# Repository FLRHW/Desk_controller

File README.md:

# Desk Controller

**A custom KiCad PCB design for a motorised sit–stand desk controller with a touchscreen human–machine interface (HMI).**

[Hardware design](https://github.com/FLRHW/Desk_controller) · [Online documentation](https://flrhw.github.io/Desk_controller/) · [Firmware repository](https://github.com/FLRHW/Desk_controller_source) · [3D renders](output/3d/) · [Manufacturing outputs](output/)

This repository contains the KiCad hardware design for a desk controller that brings together the user interface, control electronics, motor interface and end-of-travel sensing on one board. It is intended to interface with an external desk mechanism, motor/gearbox/encoder assembly and power supply. The project started as a personal engineering build; the design is published so others can inspect, learn from, or adapt it at their own risk.

Beyond the intended application, the repository documents the design workflow—from system-level architecture and hierarchical schematics through PCB layout, design checks and automated fabrication/assembly deliverables.

> **Project scope:** This repository documents the controller **hardware**. The desk mechanism, motor assembly and external power supply are shown for context and are not part of the PCB design. Do not assume the design is production-ready or safe to connect to a desk without independent electrical, mechanical and functional validation.

## System overview

The design is organised into these functional blocks:

| Block | Purpose |
| --- | --- |
| Microcontroller / control logic | Coordinates the user interface and motor-control signals. |
| Touch display | Local human–machine interface for operating the desk. |
| Servomotor interface | Motor power-drive interface and encoder signal conditioning. |
| Limit-switch interface | Connections and conditioning for end-of-travel signals. |
| 3.3 V DC/DC conversion | Low-voltage supply for the control electronics. |
| Power-supply interface | Connection to the external power source. |

See [`System_overview.kicad_sch`](System_overview.kicad_sch) and [`Block_diagram.kicad_sch`](Block_diagram.kicad_sch) for the system-level drawings. The hierarchical schematic files provide the electrical details.

## PCB renders and design outputs

The renders below are generated from the KiCad PCB design as part of the automated documentation workflow.

| Top view | Bottom view |
| --- | --- |
|  |  |

Additional renders and design files:

- [All 3D renders and models](output/3d/) — angled, top and bottom PNG views, plus the [STEP model](output/3d/Desk_controller-3D.step).
- [Fabrication documentation and files](output/fabrication/) — fabrication drawings, Gerbers and drill outputs (where generated).
- [Assembly documentation and files](output/assembly/) — assembly drawings, BOM/iBOM and placement data (where generated).
- [Design checks and build reports](output/reports/) — ERC/DRC and generation logs.
- [Browse generated outputs online](https://flrhw.github.io/Desk_controller/) — published HTML index with links to PDFs, renders, interactive BOM and downloadable manufacturing files.
- [Generated files in the repository](output/) — full output tree; the [local HTML index](output/index.html) can also be opened after cloning.
- [Native PCB layout](Desk_controller.kicad_pcb) and [hierarchical schematic](Desk_controller.kicad_sch) — editable KiCad design sources.

The generated files are published to make the design easier to review and reproduce. **Their presence does not imply that the PCB, assembly or motor-control system has been manufactured, tested or validated.** Check the current outputs and reports before considering fabrication.

## Firmware

The firmware is developed separately in **[FLRHW/Desk_controller_source](https://github.com/FLRHW/Desk_controller_source)**. It is **under development and not yet usable**. Please consult that repository for its latest implementation and status; firmware progress is intentionally not duplicated here to avoid maintaining two status reports.

## Repository contents

| Path | Description |
| --- | --- |
| [`Desk_controller.kicad_pro`](Desk_controller.kicad_pro) | KiCad project settings. |
| [`Desk_controller.kicad_sch`](Desk_controller.kicad_sch) | Root hierarchical schematic. |
| [`Desk_controller.kicad_pcb`](Desk_controller.kicad_pcb) | PCB layout. |
| `Microcontroller.kicad_sch` | Control electronics. |
| `Display.kicad_sch` | Display interface. |
| `Servomotor_interface.kicad_sch` | Motor driver and encoder interface circuitry. |
| `Limit_switch_interface.kicad_sch` | Limit-switch interface circuitry. |
| `DCDC_converter_3V3.kicad_sch` | 3.3 V supply stage. |
| `Interface_*.kicad_sch` | External connection/interface drawings. |
| `output/` | Generated documentation and manufacturing exports. |
| `config.kibot.yaml` | KiBot output and documentation configuration. |
| `.github/workflows/`, `ci/`, `scripts/`, `templates/` | Automated generation, helper scripts and drawing worksheets inherited from the KiCad starter. |

## Opening the design

1. Install [KiCad 10](https://www.kicad.org/).
2. Clone the repository:

   ```bash
   git clone https://github.com/FLRHW/Desk_controller.git
   cd Desk_controller
   ```

3. Open `Desk_controller.kicad_pro` in KiCad.
4. Open the schematic editor to navigate the hierarchical sheets, or the PCB editor to inspect the board layout.
5. Run KiCad's Electrical Rules Checker (ERC) and Design Rules Checker (DRC) after making changes, and review the reports before fabricating a board.

This is an **existing project**, not a fresh copy of the starter template: you do not need to run the template's project-creation instructions to open it.

## Generated documentation and manufacturing files

The repository uses [KiBot](https://github.com/INTI-CMNB/KiBot) and GitHub Actions to generate design documentation and manufacturing outputs. Depending on the active `config.kibot.yaml` settings and the latest completed workflow, `output/` can include:

- Schematic, assembly and fabrication PDFs
- ERC/DRC reports
- Bill of materials (BOM) and interactive HTML BOM
- Gerber files and Excellon drill files
- Pick-and-place files and 3D STEP exports
- Optional renders and manufacturing ZIP packages

Browse the [online documentation](https://flrhw.github.io/Desk_controller/), or open `output/index.html` locally after cloning. The website is updated by successful default-branch builds when GitHub Pages publishing is enabled and shows the latest deployed outputs; use a release tag for a fixed snapshot. The original template's documentation contains more details on the export system: [FLRHW KiCad Starter](https://github.com/FLRHW/KiCad_starter).

**Before ordering PCBs:** inspect the actual Gerbers, drill data, stack-up, BOM and fabrication notes. Generated outputs and a passing automation run are not substitutes for electrical and safety verification; inspect ERC/DRC reports separately.

## Development status

This repository contains an evolving hardware design. The presence of schematics, PCB files or manufacturing exports does **not** imply that a physical prototype has been built, tested or validated. Anyone building or operating hardware based on this design must independently assess the risks, verify that the complete system is safe for its intended use, and implement and validate appropriate safeguards before putting it into service. The availability of design files or manufacturing outputs is not evidence of safety or fitness for use. For firmware progress and readiness, refer to the [firmware repository](https://github.com/FLRHW/Desk_controller_source).

## Safety

Motorised desk systems can cause injury or property damage. Before operating hardware based on this design, independently verify power-stage ratings, polarity and protection; limit-switch behaviour; motor direction and feedback; fault handling; and the ability to stop motion reliably. Never rely on software alone as the sole protection against unintended travel.

In the author's personal installation, a manually operated power-disconnect switch is fitted upstream of the power supply feeding the controller. This arrangement is described for reference only and has not been established as a sufficient safety measure for other installations.

Anyone reproducing or adapting this design is responsible for independently assessing the hazards of their complete system, implementing appropriate protective measures, and verifying their effectiveness before use. No particular safety arrangement is prescribed or guaranteed by this project.

## Licensing and reuse

This repository contains material covered by **two separate licences**, according to the origin and purpose of the files:

- **Original hardware design — [CERN-OHL-P-2.0](LICENSE):** The Desk Controller schematics, PCB layout and associated original design and manufacturing files are released under the CERN Open Hardware Licence Version 2 — Permissive. The [`LICENSE`](LICENSE) file contains the hardware licence text.
- **Inherited KiCad starter infrastructure — [MIT](LICENSE-MIT):** Applicable files retained or adapted from [FLRHW/KiCad_starter](https://github.com/FLRHW/KiCad_starter), such as automation scripts, CI workflows and templates, remain under the MIT licence, with their original copyright notices preserved. The [`LICENSE-MIT`](LICENSE-MIT) file contains the corresponding MIT licence and notices.

These licences apply to their respective materials; the presence of both files does **not** mean that the entire repository is offered under a choice of either licence. Third-party dependencies or assets may have their own terms. The [firmware](https://github.com/FLRHW/Desk_controller_source) is maintained separately and is subject to the licensing terms in that repository.

**Disclaimer:** This is a personal engineering project shared **as is**, without warranty of safety, fitness for a particular purpose, completeness or correct operation. Anyone reusing, building, modifying or operating the design is responsible for their own engineering review, applicable regulatory requirements, testing and safeguards. The applicable licence texts govern warranty disclaimers and limitations of liability; this summary does not replace their terms.

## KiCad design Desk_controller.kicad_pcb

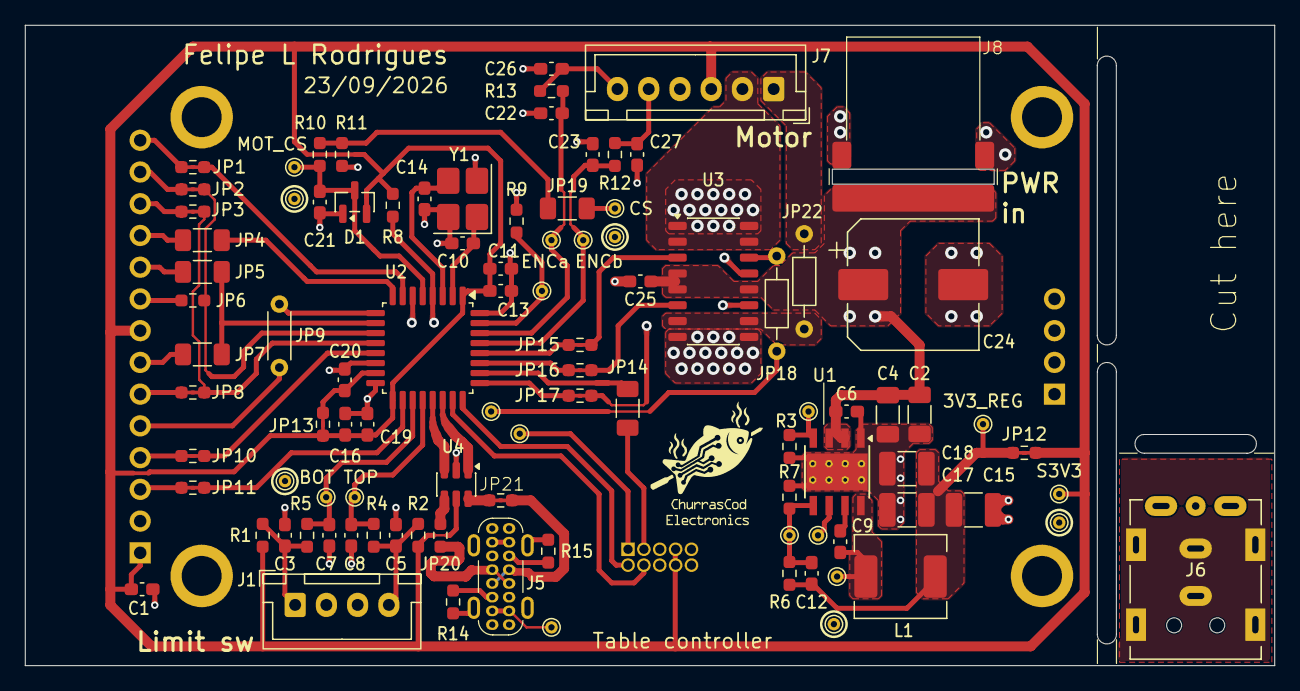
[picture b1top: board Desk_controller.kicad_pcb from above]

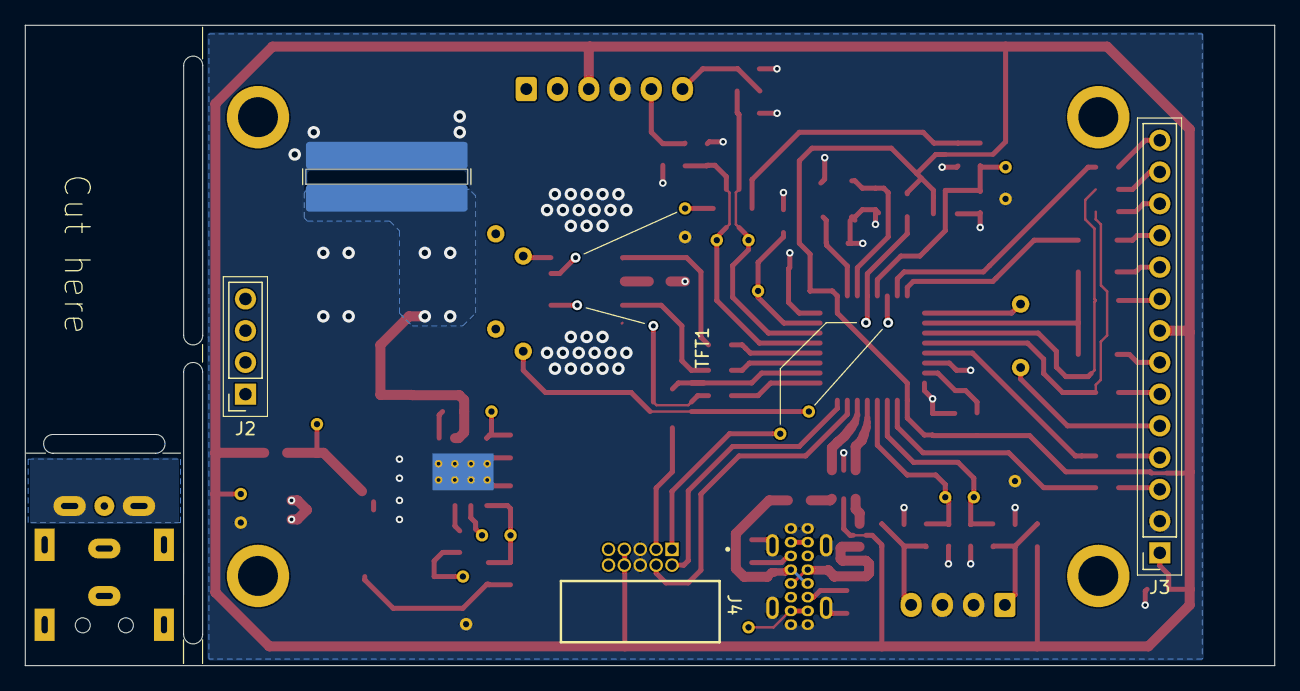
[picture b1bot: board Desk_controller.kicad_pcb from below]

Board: 2 copper layers, 100.0 x 51.2 mm, 105 parts (7 on the bottom side), 74 nets.

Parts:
C1, C6, C9, C13, C19, C20, C25: 100n; C_0603_1608Metric_Pad1.08x0.95mm_HandSolder
C2, C4: 4.7u; C_1206_3216Metric_Pad1.33x1.80mm_HandSolder
C3, C5, C26, C27: 10n; C_0603_1608Metric_Pad1.08x0.95mm_HandSolder
C7, C8, C21, C22, C23: 1n; C_0603_1608Metric_Pad1.08x0.95mm_HandSolder
C10, C14: 22p; C_0603_1608Metric_Pad1.08x0.95mm_HandSolder
C11, C16: 1u; C_0603_1608Metric_Pad1.08x0.95mm_HandSolder
C12: 33p; C_0603_1608Metric_Pad1.08x0.95mm_HandSolder
C15, C17, C18: 22u; C_1210_3225Metric_Pad1.33x2.70mm_HandSolder
C24: 220u; CP_Elec_10x10
D1: BAV99; SOT-23
J1: B4B XH A; JST_XH_B4B-XH-A_1x04_P2.50mm_Vertical
J2: 01x04 socket; PinSocket_1x04_P2.54mm_Vertical
J3: 01x14 socket; PinSocket_1x14_P2.54mm_Vertical
J4: HX JN1.27-2x5 WZ H4.9; JN1.27-2x5 WZ H4.9
J5: USB_C_Receptacle_USB2.0_16P; USB_C_socket_16P_vertical
J6: Dell DC jack
J7: B6B XH A; JST_XH_B6B-XH-A_1x06_P2.50mm_Vertical
J8: DC barrel assy; Dell_barrel_assy
JP1, JP2, JP3, JP8, JP10, JP11, JP12, JP13, JP15, JP16, JP17, JP21: 0R; Jumper_0603
JP4, JP5, JP7, JP14, JP19: 0R; R_1206_3216Metric_Pad1.30x1.75mm_HandSolder
JP6, JP20: 0R; R_0603_1608Metric_Pad0.98x0.95mm_HandSolder
JP9: 0R; R_Axial_DIN0204_L3.6mm_D1.6mm_P5.08mm_Horizontal
JP18, JP22: 0R; R_Axial_DIN0204_L3.6mm_D1.6mm_P7.62mm_Horizontal
JP23: 0R; Wire_9.603mm
JP24: 0R; Wire_6.310mm
JP25: 0R; Wire_9.532mm
JP26: 0R; Wire_6.853x8.890mm
L1: 10u; L_Bourns_SRP6540
R1, R2, R7, R8, R9: 10k; R_0603_1608Metric_Pad0.98x0.95mm_HandSolder
R3: 64.9k; R_0603_1608Metric_Pad0.98x0.95mm_HandSolder
R4, R5, R10, R12, R13: 2k2; R_0603_1608Metric_Pad0.98x0.95mm_HandSolder
R6: 23.2k; R_0603_1608Metric_Pad0.98x0.95mm_HandSolder
R11: 820; R_0603_1608Metric_Pad0.98x0.95mm_HandSolder
R14, R15: 5k1; R_0603_1608Metric_Pad0.98x0.95mm_HandSolder
TFT1: TFT_2.4in_320x240; Display_240x320_ILI9341_2.4in_no_pads
TP1, TP2, TP3, TP4, TP5, TP6, TP7, TP8, TP9, TP10, TP11, TP12, TP13, TP14, TP15, TP16, TP17, TP18, TP19, TP20, TP21: TestPoint; TestPoint_THTPad_D1.0mm_Drill0.5mm
U1: LMR380x0; Texas_HSOP-8-1EP_3.9x4.9mm_P1.27mm_ThermalVias_w_step
U2: STM32G431K8T; LQFP-32_7x7mm_P0.8mm
U3: VNH7070; JEITA_SOIC-16_3.9x9.9mm_P1.27mm
U4: USBLC6-2SC6; SOT-23-6
Y1: 20 MHz; Crystal_SMD_3225-4Pin_3.2x2.5mm_HandSoldering

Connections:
/System overview/Block diagram/DCDC converter 3V3/3V3_REG: C12.1, C15.1, C17.1, C18.1, JP12.1, L1.2, R6.1, TP10.1 (1_1)
/System overview/Block diagram/DCDC converter 3V3/FB: C12.2, R6.2, R7.1, TP5.1 (1_1), U1.5 (FB)
/System overview/Block diagram/DCDC converter 3V3/GND_2: J6.3 (-), J6.SH
/System overview/Block diagram/DCDC converter 3V3/PG: TP1.1 (1_1), U1.6 (PG)
/System overview/Block diagram/DCDC converter 3V3/RT: R3.1, TP2.1 (1_1), U1.4 (RT/SYNC)
/System overview/Block diagram/DCDC converter 3V3/SW: C9.2, L1.1, TP6.1 (1_1), U1.8 (SW)
/System overview/Block diagram/Display/DISP_CS: JP11.1, U2.18 (PA8)
/System overview/Block diagram/Display/DISP_DC: JP9.1, U2.9 (PA4)
/System overview/Block diagram/Display/DISP_MISO: JP2.1, JP6.1, U2.11 (PA6)
/System overview/Block diagram/Display/DISP_MOSI: JP3.1, JP8.1, U2.12 (PA7)
/System overview/Block diagram/Display/DISP_RST: JP10.1, U2.13 (PB0)
/System overview/Block diagram/Display/DISP_SCK: JP5.1, JP7.1, U2.10 (PA5)
/System overview/Block diagram/Display/TCH_CS: JP4.1, U2.8 (PA3)
/System overview/Block diagram/Display/TCH_IRQ: JP1.1, U2.7 (PA2)
/System overview/Block diagram/GND: C1.2, C2.2, C3.2, C4.2, C5.2, C6.2, C7.2, C8.2, C10.2, C11.2, C13.2, C14.2, C15.2, C16.2, C17.2, C18.2, C19.2, C20.2, C21.2, C22.2, C23.2, C24.2, C25.2, C26.2, C27.2, D1.1 (K), J1.2, J1.3, J3.2, J4.5, J4.6, J5.A1 (GND), J5.A12 (GND), J5.B1 (GND), J5.B12 (GND), J5.SH (SHIELD), J7.4, J8.2 (-), R3.2, R7.2, R9.2, R11.2, R14.2, R15.2, TP7.1 (1_1), TP18.1 (1_1), TP19.1 (1_1), TP20.1 (1_1), TP21.1 (1_1), U1.1 (GND), U1.9 (EP), U2.14 (VSSA), U2.16 (VSS), U2.32 (VSS), U3.1 (GNDa), U3.8 (GNDb), U3.9 (GNDb), U3.16 (GNDa), U4.2 (GND), Y1.2 (G), Y1.4 (G)
/System overview/Block diagram/Limit switch interface/BOT_EOT: C3.1, J1.1, R1.2, R5.1
/System overview/Block diagram/Limit switch interface/BOT_filt: C7.1, R5.2, TP4.1 (1_1), U2.19 (PA9)
/System overview/Block diagram/Limit switch interface/TOP_EOT: C5.1, J1.4, R2.2, R4.1
/System overview/Block diagram/Limit switch interface/TOP_filt: C8.1, R4.2, TP3.1 (1_1), U2.20 (PA10)
/System overview/Block diagram/Microcontroller/BOOT0: R9.1, TP9.1 (1_1), U2.31 (PB8)
/System overview/Block diagram/Microcontroller/CC1: J5.A5 (CC1), R14.1
/System overview/Block diagram/Microcontroller/CC2: J5.B5 (CC2), R15.1
/System overview/Block diagram/Microcontroller/D+: J5.A6 (D+), J5.B6 (D+), JP21.1
/System overview/Block diagram/Microcontroller/D+': JP21.2, U4.6 (I/O1)
/System overview/Block diagram/Microcontroller/D-: J5.A7 (D-), J5.B7 (D-), JP20.1
/System overview/Block diagram/Microcontroller/D-': JP20.2, U4.4 (I/O2)
/System overview/Block diagram/Microcontroller/ENCa_filt: C23.1, R12.1, TP12.1 (1_1), U2.29 (PB6)
/System overview/Block diagram/Microcontroller/ENCb_filt: C22.1, R13.1, TP13.1 (1_1), U2.30 (PB7)
/System overview/Block diagram/Microcontroller/INa: JP15.1, U2.28 (PB5)
/System overview/Block diagram/Microcontroller/INb: JP16.1, U2.27 (PB4)
/System overview/Block diagram/Microcontroller/MOT_CS: C21.1, D1.3 (K), R10.1, TP14.1 (1_1), U2.5 (PA0)
/System overview/Block diagram/Microcontroller/NRST: JP26.1, R8.2, U2.4 (PG10)
/System overview/Block diagram/Microcontroller/NRST': J4.1, JP26.2, TP8.1 (1_1)
/System overview/Block diagram/Microcontroller/PWM: JP17.1, U2.25 (PA15)
/System overview/Block diagram/Microcontroller/S3V3_A: C20.1, JP13.2, U2.15 (VDDA)
/System overview/Block diagram/Microcontroller/SEL0: JP25.1, U2.6 (PA1)
/System overview/Block diagram/Microcontroller/SWDCLK: J4.2, U2.24 (PA14)
/System overview/Block diagram/Microcontroller/SWDIO: J4.4, U2.23 (PA13)
/System overview/Block diagram/Microcontroller/SWO: JP14.1, U2.26 (PB3)
/System overview/Block diagram/Microcontroller/SWO': J4.3, JP14.2
/System overview/Block diagram/Microcontroller/USB_DM: U2.21 (PA11), U4.3 (I/O2)
/System overview/Block diagram/Microcontroller/USB_DP: U2.22 (PA12), U4.1 (I/O1)
/System overview/Block diagram/Microcontroller/XIN: C10.1, U2.2 (PF0), Y1.1
/System overview/Block diagram/Microcontroller/XOUT: C14.1, U2.3 (PF1), Y1.3
/System overview/Block diagram/S3V3: C1.1, C11.1, C13.1, C16.1, C19.1, D1.2 (A), J3.1, J3.8, J4.7, J4.8, J7.3, JP12.2, JP13.1, R1.1, R2.1, R8.1, TP17.1 (1_1), U2.1 (VDD), U2.17 (VDD), U4.5 (VBUS)
/System overview/Block diagram/S19V5: C2.1, C4.1, C6.1, C24.1, C25.1, J8.1 (+), U1.2 (EN), U1.3 (VIN), U3.4 (VCC), U3.5 (VCC), U3.12 (VCC)
/System overview/Block diagram/Servomotor interface/CS': JP19.2, JP23.1, TP15.1 (1_1)
/System overview/Block diagram/Servomotor interface/ENCa: C27.1, J7.5, R12.2
/System overview/Block diagram/Servomotor interface/ENCb: C26.1, J7.6, R13.2
/System overview/Block diagram/Servomotor interface/INa': JP15.2, U3.3 (INa)
/System overview/Block diagram/Servomotor interface/INb': JP16.2, U3.6 (INb)
/System overview/Block diagram/Servomotor interface/OUTa: J7.2, U3.2 (OUTa), U3.15 (OUTa)
/System overview/Block diagram/Servomotor interface/OUTb: J7.1, JP22.1
/System overview/Block diagram/Servomotor interface/OUTb': JP22.2, U3.7 (OUTb), U3.10 (OUTb)
/System overview/Block diagram/Servomotor interface/PWM': JP17.2, JP24.1
/System overview/Block diagram/Servomotor interface/PWM'': JP24.2, U3.11 (PWM)
/System overview/Block diagram/Servomotor interface/SEL0': JP18.2, JP25.2, TP11.1 (1_1)
/System overview/Block diagram/Servomotor interface/SEL0'': JP18.1, U3.14 (SEL0)
unnamed: J3.3, JP11.2
unnamed: J3.4, JP10.2
unnamed: J3.5, JP9.2
unnamed: J3.6, JP8.2
unnamed: J3.7, JP7.2
unnamed: J3.9, JP6.2
unnamed: J3.10, JP5.2
unnamed: J3.11, JP4.2
unnamed: J3.12, JP3.2
unnamed: J3.13, JP2.2
unnamed: J3.14, JP1.2
unnamed: J5.A4 (VBUS), J5.B9 (VBUS), TP16.1 (1_1)
unnamed: J5.A9 (VBUS), J5.B4 (VBUS)
unnamed: JP19.1, R10.2, R11.1
unnamed: C9.1, U1.7 (BOOT)
unnamed: JP23.2, U3.13 (CS)

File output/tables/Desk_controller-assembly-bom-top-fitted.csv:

References,Qty,Value,Footprint,MPN,Manufacturer,Status
C1 C6 C9 C13 C19 C20 C25,7,100n,C_0603_1608Metric_Pad1.08x0.95mm_HandSolder,AC0603KRX7R9BB104,Yageo, 
C3 C5 C26 C27,4,10n,C_0603_1608Metric_Pad1.08x0.95mm_HandSolder,AC0603KRX7R9BB103,Yageo, 
C7 C8 C21 C22 C23,5,1n,C_0603_1608Metric_Pad1.08x0.95mm_HandSolder,AC0603KRX7R9BB102,Yageo, 
C11 C16,2,1u,C_0603_1608Metric_Pad1.08x0.95mm_HandSolder,AC0603KRX7R7BB105,Yageo, 
C24,1,220u,CP_Elec_10x10,EEE-FK1H221P,Panasonic, 
C10 C14,2,22p,C_0603_1608Metric_Pad1.08x0.95mm_HandSolder,AC0603JRNPO9BN220,Yageo, 
C15 C17 C18,3,22u,C_1210_3225Metric_Pad1.33x2.70mm_HandSolder,MCAST32MSB7226KPNA01,TAIYO YUDEN, 
C12,1,33p,C_0603_1608Metric_Pad1.08x0.95mm_HandSolder,AC0603JRNPO9BN330,Yageo, 
C2 C4,2,4.7u,C_1206_3216Metric_Pad1.33x1.80mm_HandSolder,C1206C475K5RACAUTO,KEMET, 
D1,1,BAV99,SOT-23,BAV99Q-7-F,Diodes Inc, 
J1,1,B4B XH A,JST_XH_B4B-XH-A_1x04_P2.50mm_Vertical,B4B XH A,JST, 
J7,1,B6B XH A,JST_XH_B6B-XH-A_1x06_P2.50mm_Vertical,B6B XH A,JST, 
J8,1,DC barrel assy,Dell_barrel_assy,NA,NA, 
J6,1,Dell DC jack,Dell DC jack,Barrel jack,Dell, 
J5,1,USB_C_Receptacle_USB2.0_16P,USB_C_socket_16P_vertical,TFKH5-16L4CC-65,ChengHaoRan, 
JP4 JP5 JP7 JP14 JP19,5,0R,R_1206_3216Metric_Pad1.30x1.75mm_HandSolder,Hand cut wire,NA, 
JP18 JP22,2,0R,R_Axial_DIN0204_L3.6mm_D1.6mm_P7.62mm_Horizontal,Hand cut wire,NA, 
JP6 JP20,2,0R,R_0603_1608Metric_Pad0.98x0.95mm_HandSolder,RC0603JR-130RP,Yageo, 
JP26,1,0R,Wire_6.853x8.890mm,Hand cut wire,NA, 
JP9,1,0R,R_Axial_DIN0204_L3.6mm_D1.6mm_P5.08mm_Horizontal,Hand cut wire,NA, 
L1,1,10u,L_Bourns_SRP6540,SRP6540-100M,Bourns, 
R1 R2 R7 R8 R9,5,10k,R_0603_1608Metric_Pad0.98x0.95mm_HandSolder,AC0603FR-0710KL,YAGEO, 
R6,1,23.2k,R_0603_1608Metric_Pad0.98x0.95mm_HandSolder,AC0603FR-0723K2L,YAGEO, 
R4 R5 R10 R12 R13,5,2k2,R_0603_1608Metric_Pad0.98x0.95mm_HandSolder,AC0603FR-072K2L,YAGEO, 
R14 R15,2,5k1,R_0603_1608Metric_Pad0.98x0.95mm_HandSolder,AC0603FR-075K1L,YAGEO, 
R3,1,64.9k,R_0603_1608Metric_Pad0.98x0.95mm_HandSolder,AC0603FR-0764K9L,YAGEO, 
R11,1,820,R_0603_1608Metric_Pad0.98x0.95mm_HandSolder,AC0603FR-07820RL,YAGEO, 
U1,1,LMR380x0,Texas_HSOP-8-1EP_3.9x4.9mm_P1.27mm_ThermalVias_w_step,LMR38020FDDAR,Texas instruments, 
U2,1,STM32G431K8T,LQFP-32_7x7mm_P0.8mm,STM32G431K8T6,ST, 
U4,1,USBLC6-2SC6,SOT-23-6,USBLC6-2SC6,ST, 
U3,1,VNH7070,JEITA_SOIC-16_3.9x9.9mm_P1.27mm,VNH7070,ST, 
Y1,1,20 MHz,Crystal_SMD_3225-4Pin_3.2x2.5mm_HandSoldering,CX3225SB20000H0FLJCC,KYOCERA AVX,
